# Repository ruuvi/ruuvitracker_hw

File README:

This repository includes RuuviTracker's KiCad project files.

More info about RuuviTracker project: http://www.ruuvitracker.fi

Licensed using: Attribution-NonCommercial-ShareAlike 3.0 Unported (CC BY-NC-SA 3.0)

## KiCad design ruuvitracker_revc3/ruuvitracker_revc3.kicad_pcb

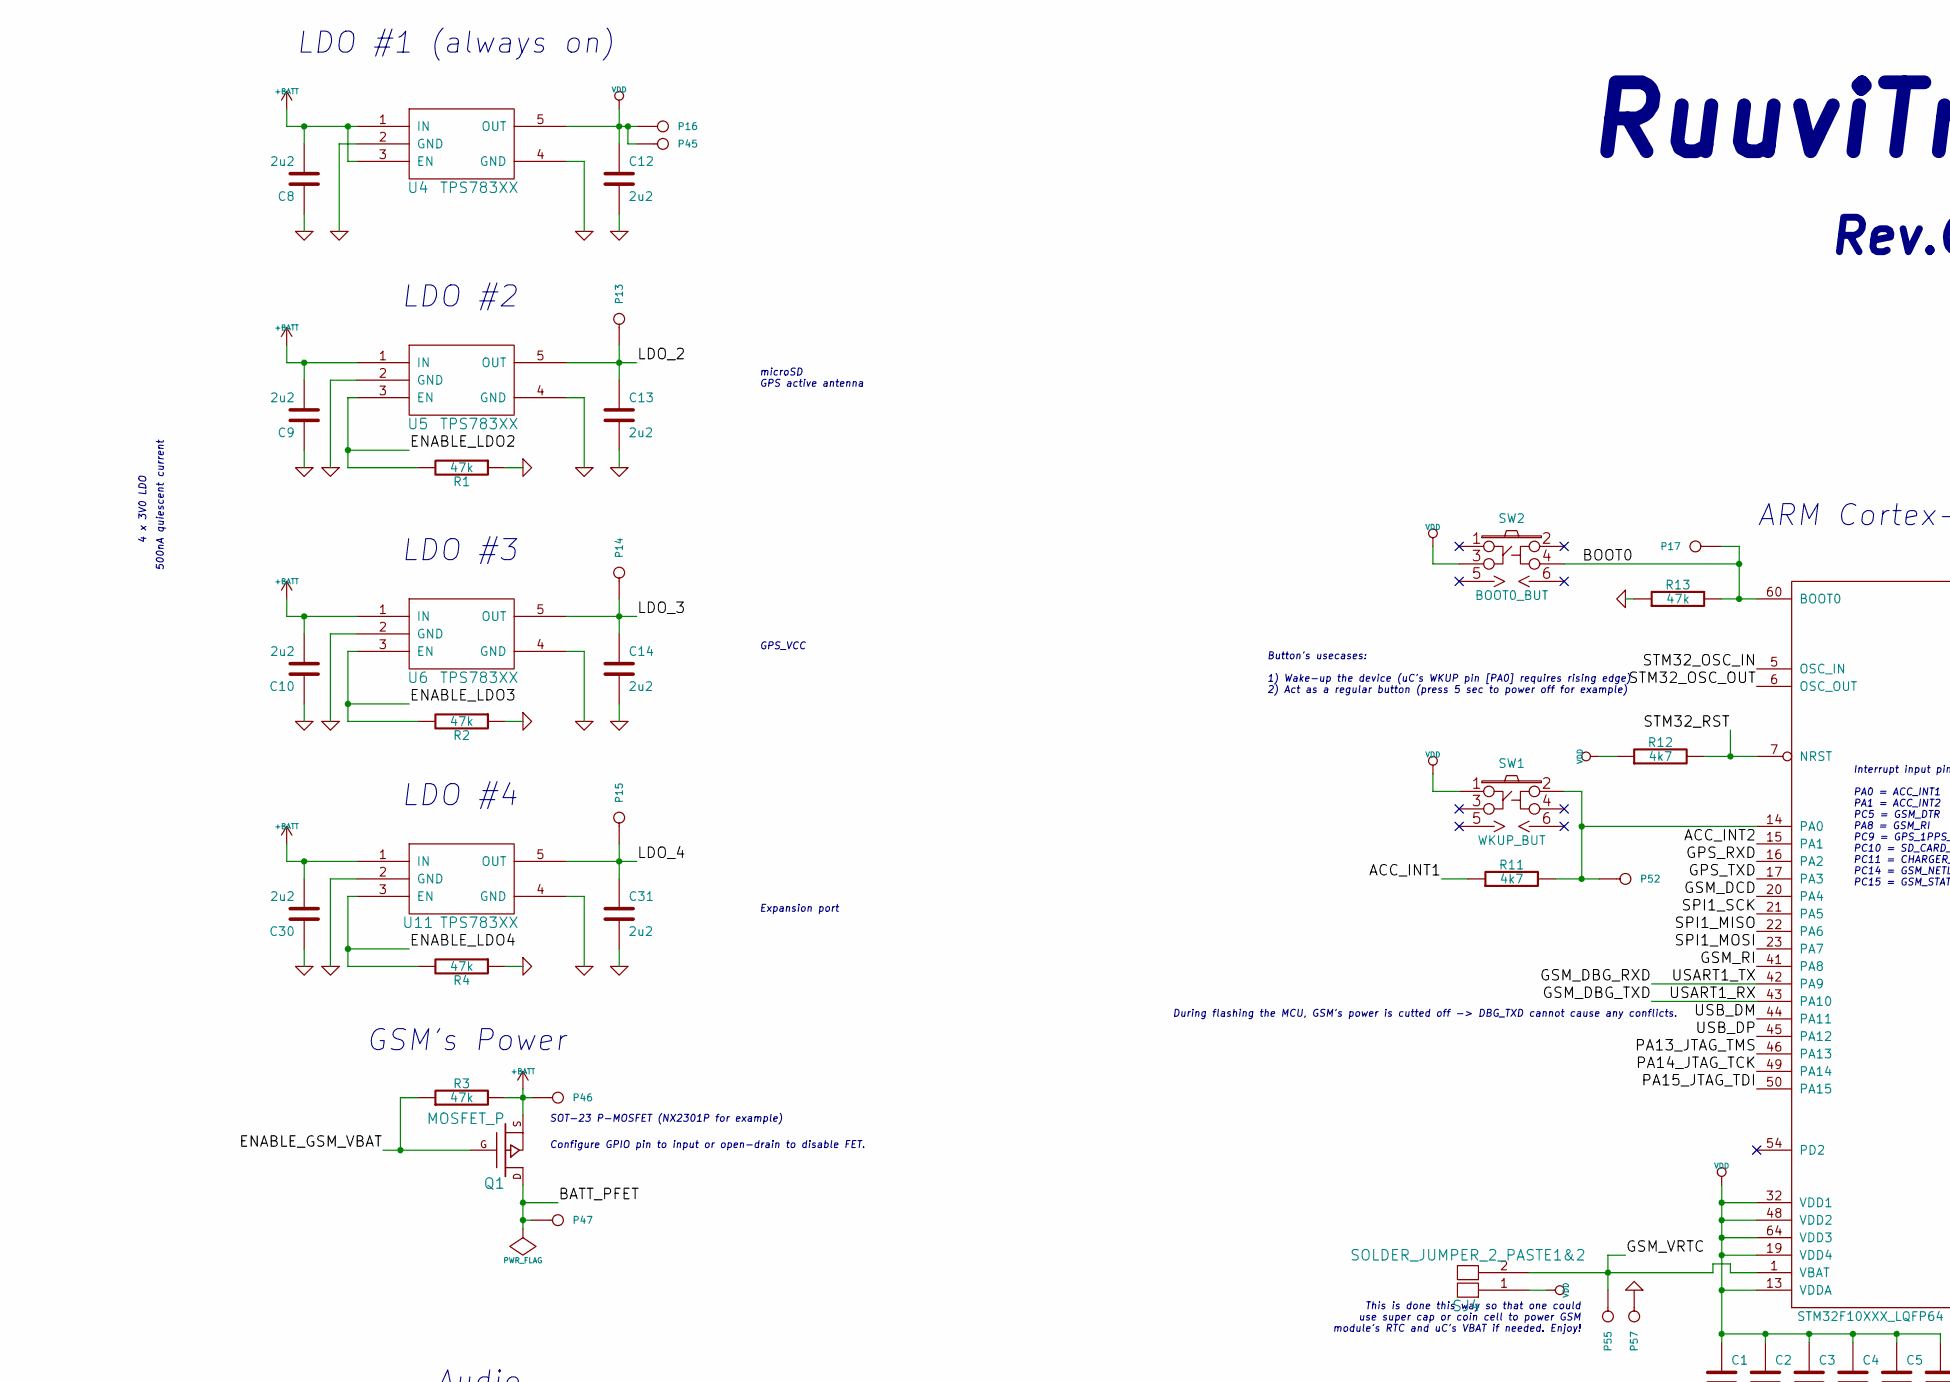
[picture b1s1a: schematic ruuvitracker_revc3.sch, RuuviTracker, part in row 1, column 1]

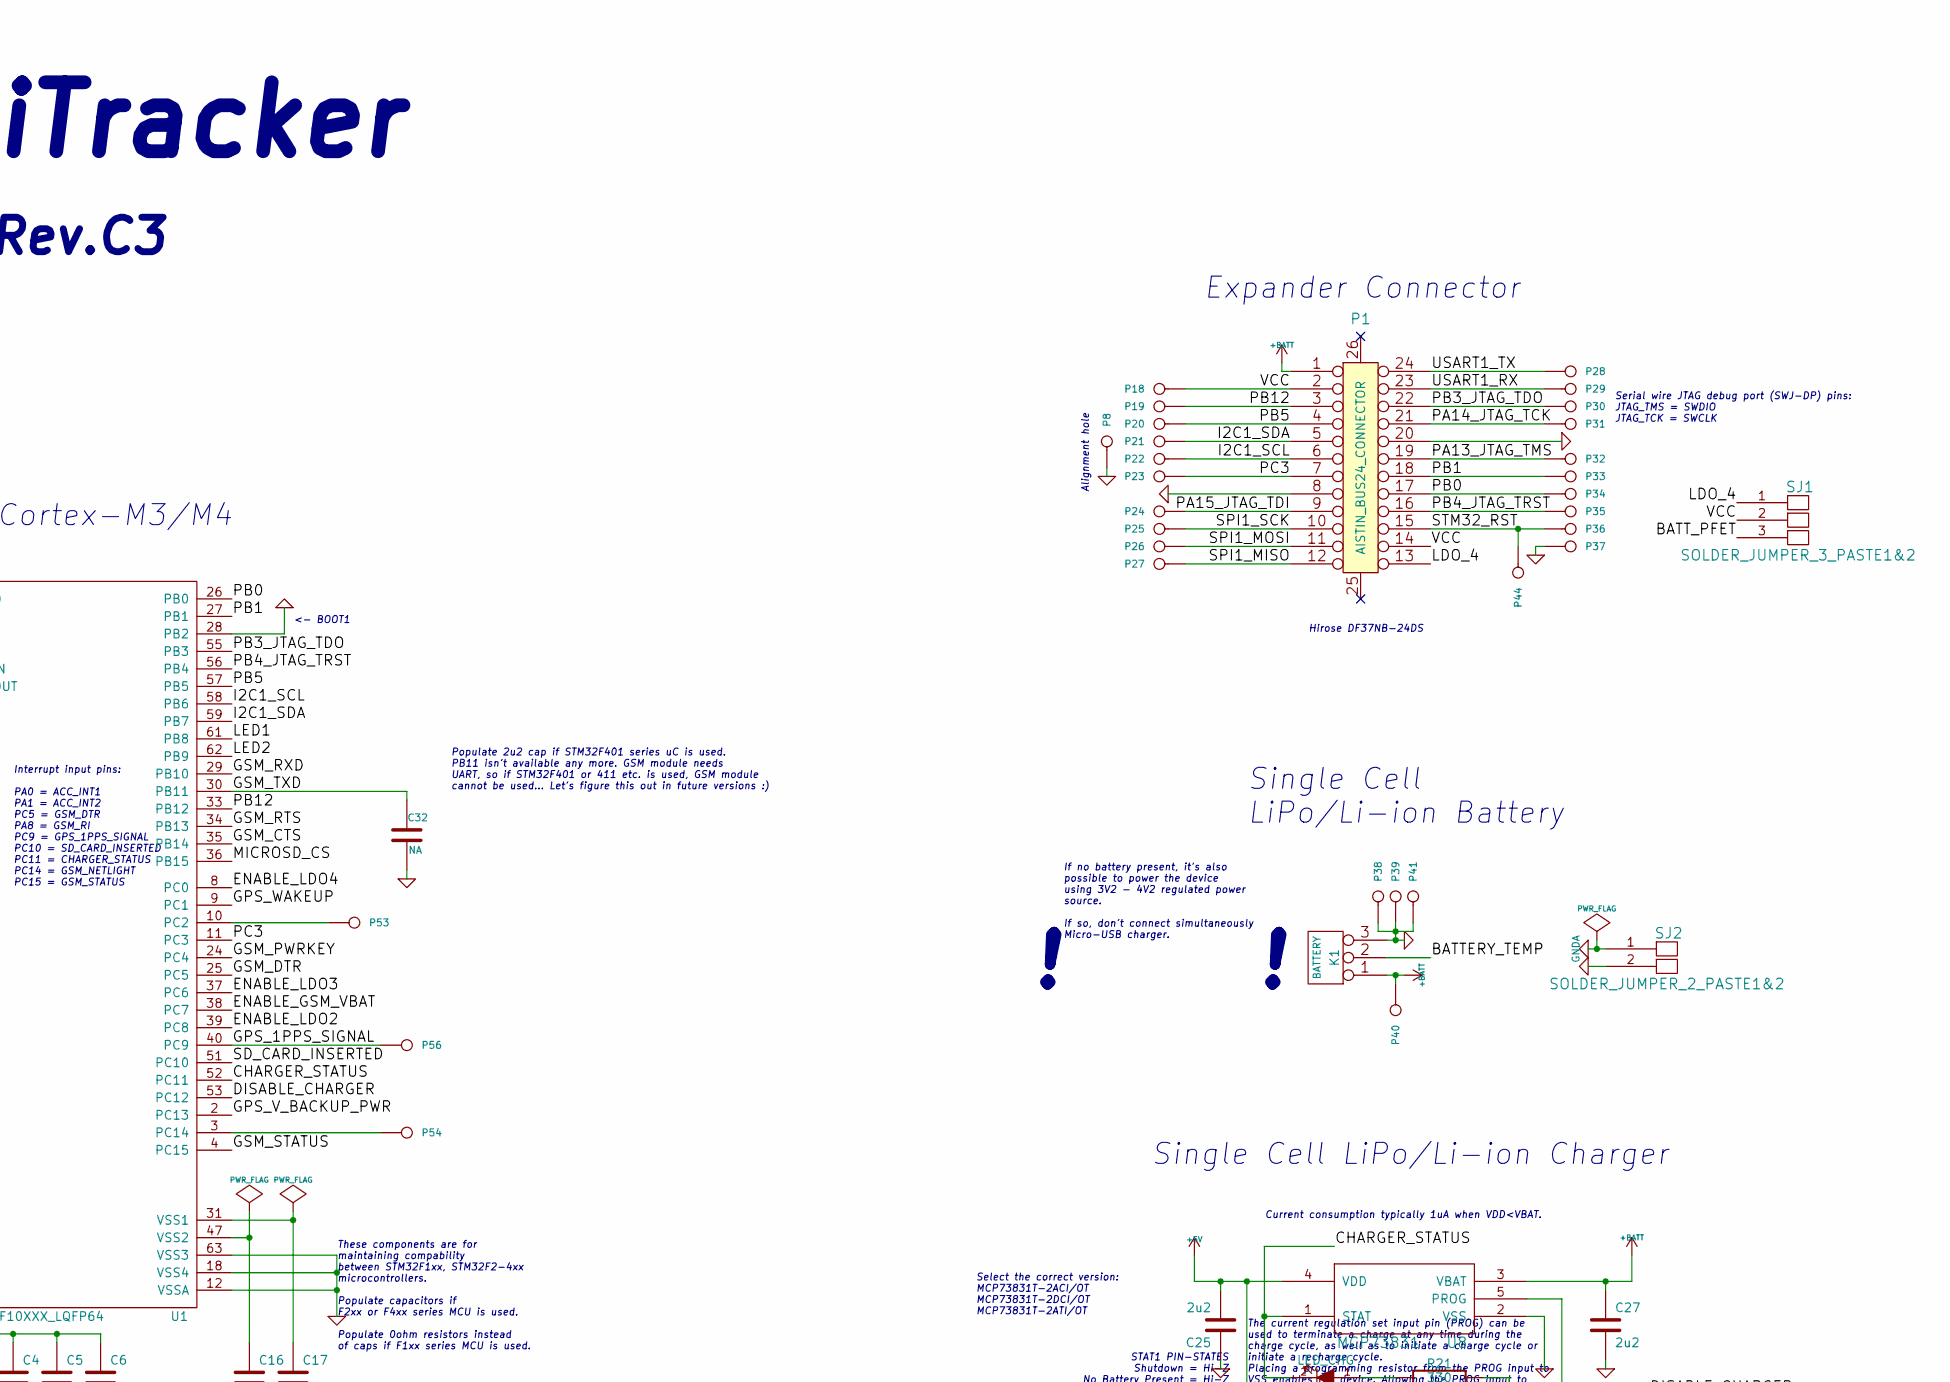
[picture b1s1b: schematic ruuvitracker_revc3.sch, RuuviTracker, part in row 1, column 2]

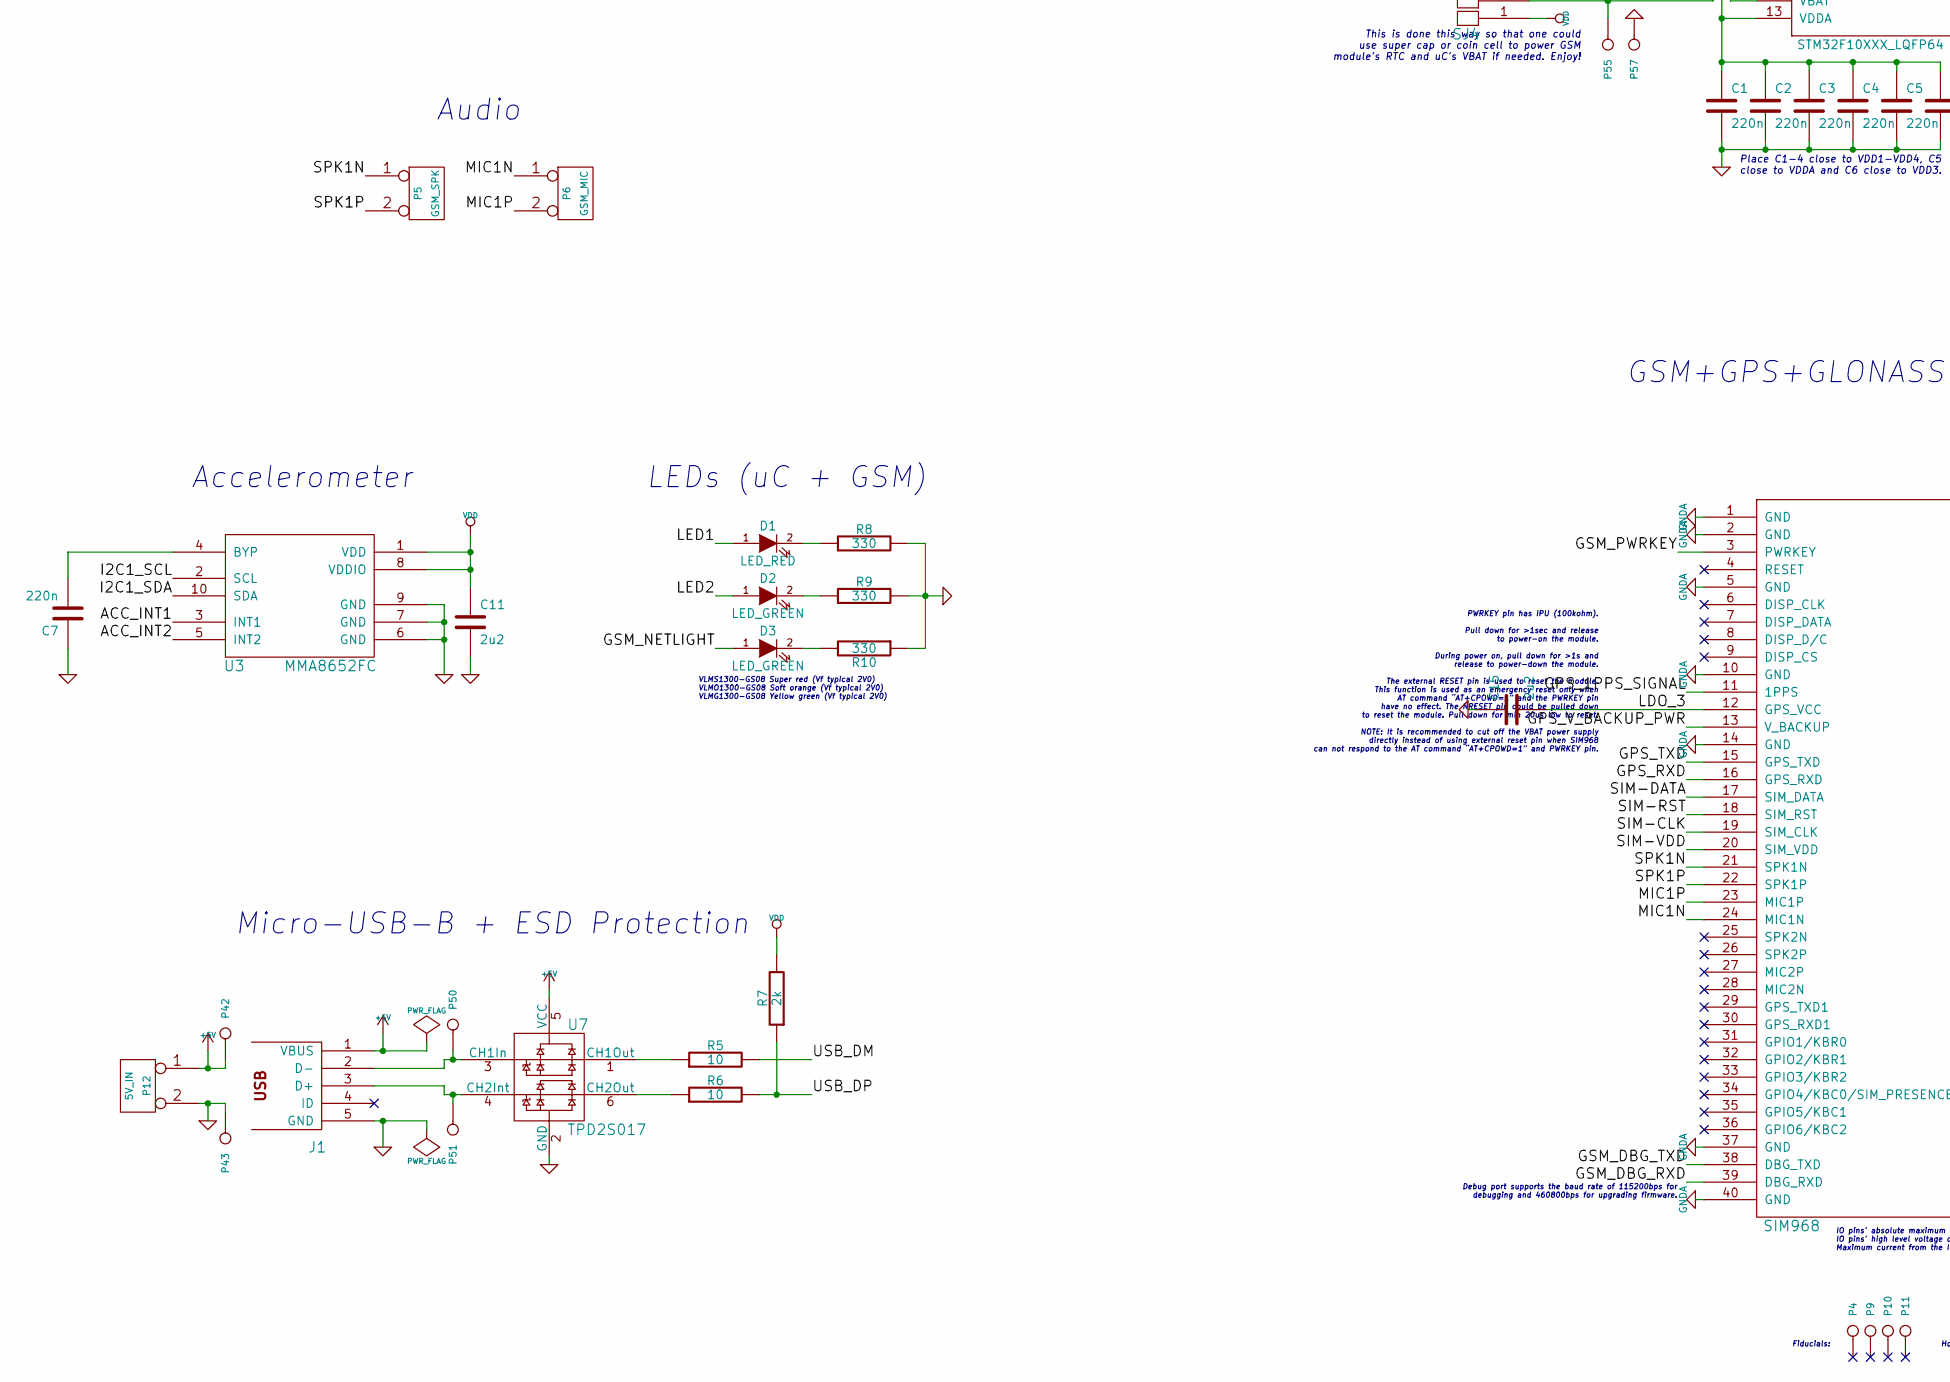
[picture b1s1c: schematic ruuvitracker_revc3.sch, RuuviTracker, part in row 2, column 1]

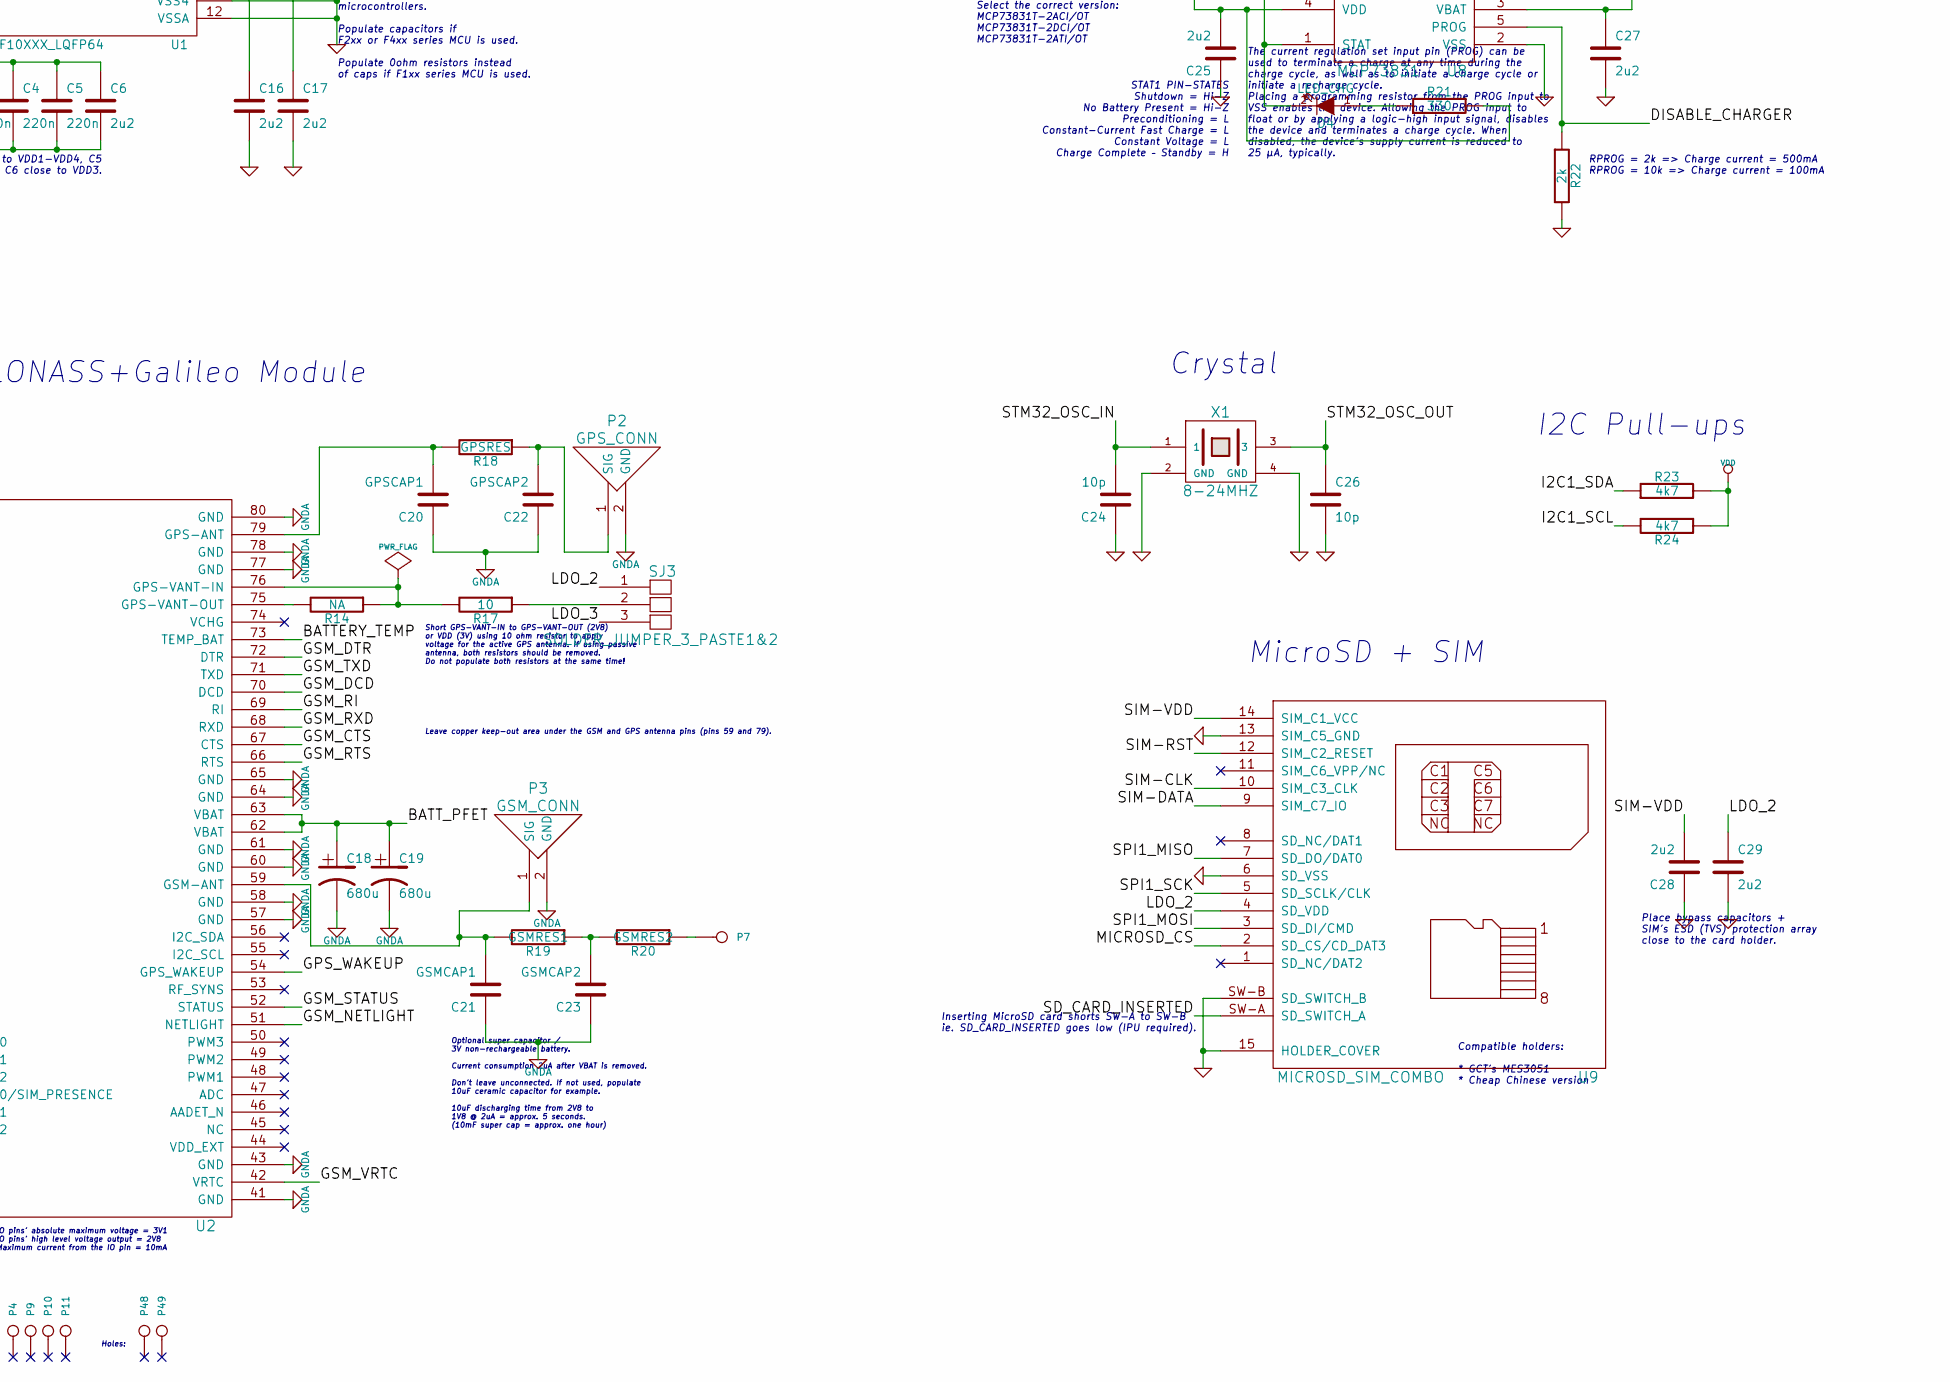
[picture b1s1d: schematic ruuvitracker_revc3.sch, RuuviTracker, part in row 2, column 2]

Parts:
C1, C2, C3, C4, C5, C7: 220n
C6, C8, C9, C10, C11, C12, C13, C14, C15, C16, C17, C25, C27, C28, C29, C30, C31: 2u2
C18, C19: 680u
C20: GPSCAP1
C21: GSMCAP1
C22: GPSCAP2
C23: GSMCAP2
C24, C26: 10p
C32: NA
D1: LED_RED
D2, D3: LED_GREEN
D4: LED_CHG
J1: USB_MICRO_B
K1: BATTERY
P1: AISTIN_BUS24_CONNECTOR
P2: GPS_CONN
P3: GSM_CONN
P4, P9, P10, P11: FIDU
P5: GSM_SPK
P6: GSM_MIC
P7: GSM_ANT
P8: ALIGNMENT
P12: 5V_IN
P13, P14, P15, P16, P17, P18, P19, P20, P21, P22, P23, P24, P25, P26, P27, P28, P29, P30, P31, P32, P33, P34, P35, P36, P37, P38, P39, P40, P41, P42, P43, P44, P45, P46, P47, P50, P51, P52, P53, P54, P55, P56, P57: CONN_1
P48, P49: HOLE
Q1: MOSFET_P
R1, R2, R3, R4, R13: 47k
R5, R6, R17: 10
R7, R22: 2k
R8, R9, R10, R21: 330
R11, R12, R23, R24: 4k7
R14: NA
R18: GPSRES
R19: GSMRES1
R20: GSMRES2
SJ1, SJ3: SOLDER_JUMPER_3_PASTE1&2
SJ2, SJ4: SOLDER_JUMPER_2_PASTE1&2
SW1: WKUP_BUT
SW2: BOOT0_BUT
U1: STM32F10XXX_LQFP64
U2: SIM968
U3: MMA8652FC
U4, U5, U6, U11: TPS783XX
U7: TPD2S017
U8: MCP73831
U9: MICROSD_SIM_COMBO
X1: 8-24MHZ

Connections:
+5V: C25.2, J1.1 (VBUS), P12.1, P42.1, R21.2, U7.5 (VCC), U8.4 (VDD)
+BATT: C8.2, C9.2, C10.2, C27.1, C30.2, K1.1, P1.1, P40.1, P46.1, Q1.S, R3.2, U4.1 (IN), U4.3 (EN), U5.1 (IN), U6.1 (IN), U8.3 (VBAT), U11.1 (IN)
/ACC_INT1: R11.1, U3.3 (INT1)
/ACC_INT2: U1.15 (PA1), U3.5 (INT2)
/BATTERY_TEMP: K1.2 (PM), U2.73 (TEMP_BAT)
/BATT_PFET: C18.1, C19.1, P47.1, Q1.D, SJ1.3, U2.62 (VBAT), U2.63 (VBAT)
/BOOT0: P17.1, R13.2, SW2.4, U1.60 (BOOT0)
/CHARGER_STATUS: D4.2 (K), U1.52 (PC11), U8.1 (STAT)
/DISABLE_CHARGER: R22.1, U1.53 (PC12), U8.5 (PROG)
/ENABLE_GSM_VBAT: Q1.G, R3.1, U1.38 (PC7)
/ENABLE_LDO2: R1.2, U1.39 (PC8), U5.3 (EN)
/ENABLE_LDO3: R2.2, U1.37 (PC6), U6.3 (EN)
/ENABLE_LDO4: R4.2, U1.8 (PC0), U11.3 (EN)
/GPS_1PPS_SIGNAL: P56.1, U1.40 (PC9), U2.11 (1PPS)
/GPS_RXD: U1.16 (PA2), U2.16 (GPS_RXD)
/GPS_TXD: U1.17 (PA3), U2.15 (GPS_TXD)
/GPS_V_BACKUP_PWR: U1.2 (PC13), U2.13 (V_BACKUP)
/GPS_WAKEUP: U1.9 (PC1), U2.54 (GPS_WAKEUP)
/GSM_CTS: U1.35 (PB14), U2.67 (CTS)
/GSM_DBG_RXD: P1.24, P28.1, U1.42 (PA9), U2.39 (DBG_RXD)
/GSM_DBG_TXD: P1.23, P29.1, U1.43 (PA10), U2.38 (DBG_TXD)
/GSM_DCD: U1.20 (PA4), U2.70 (DCD)
/GSM_DTR: U1.25 (PC5), U2.72 (DTR)
/GSM_NETLIGHT: D3.1 (A), U2.51 (NETLIGHT)
/GSM_PWRKEY: U1.24 (PC4), U2.3 (PWRKEY)
/GSM_RI: U1.41 (PA8), U2.69 (RI)
/GSM_RTS: U1.34 (PB13), U2.66 (RTS)
/GSM_RXD: U1.29 (PB10), U2.68 (RXD)
/GSM_STATUS: U1.4 (PC15), U2.52 (STATUS)
/GSM_TXD: C32.1, U1.30 (PB11), U2.71 (TXD)
/GSM_VRTC: P55.1, SJ4.2, U1.1 (VBAT), U2.42 (VRTC)
/I2C1_SCL: P1.6, P22.1, R24.2, U1.58 (PB6), U3.2 (SCL)
/I2C1_SDA: P1.5, P21.1, R23.1, U1.59 (PB7), U3.10 (SDA)
/LDO_2: C13.1, C29.1, P13.1, SJ3.1, U5.5 (OUT), U9.4 (SD_VDD)
/LDO_3: C14.1, C15.2, P14.1, SJ3.3, U2.12 (GPS_VCC), U6.5 (OUT)
/LDO_4: C31.1, P1.13, P15.1, SJ1.1, U11.5 (OUT)
/LED1: D1.1 (A), U1.61 (PB8)
/LED2: D2.1 (A), U1.62 (PB9)
/MIC1N: P6.1, U2.24 (MIC1N)
/MIC1P: P6.2 (PM), U2.23 (MIC1P)
/MICROSD_CS: U1.36 (PB15), U9.2 (SD_CS/CD_DAT3)
/PA13_JTAG_TMS: P1.19, P32.1, U1.46 (PA13)
/PA14_JTAG_TCK: P1.21, P31.1, U1.49 (PA14)
/PA15_JTAG_TDI: P1.9, P24.1, U1.50 (PA15)
/PB0: P1.17, P34.1, U1.26 (PB0)
/PB1: P1.18, P33.1, U1.27 (PB1)
/PB3_JTAG_TDO: P1.22, P30.1, U1.55 (PB3)
/PB4_JTAG_TRST: P1.16, P35.1, U1.56 (PB4)
/PB5: P1.4, P20.1, U1.57 (PB5)
/PB12: P1.3, P19.1, U1.33 (PB12)
/PC3: P1.7, P23.1, U1.11 (PC3)
/SD_CARD_INSERTED: U1.51 (PC10), U9.SW-A (SD_SWITCH_A)
/SIM-CLK: U2.19 (SIM_CLK), U9.10 (SIM_C3_CLK)
/SIM-DATA: U2.17 (SIM_DATA), U9.9 (SIM_C7_IO)
/SIM-RST: U2.18 (SIM_RST), U9.12 (SIM_C2_RESET)
/SIM-VDD: C28.2, U2.20 (SIM_VDD), U9.14 (SIM_C1_VCC)
/SPI1_MISO: P1.12, P27.1, U1.22 (PA6), U9.7 (SD_DO/DAT0)
/SPI1_MOSI: P1.11, P26.1, U1.23 (PA7), U9.3 (SD_DI/CMD)
/SPI1_SCK: P1.10, P25.1, U1.21 (PA5), U9.5 (SD_SCLK/CLK)
/SPK1N: P5.1, U2.21 (SPK1N)
/SPK1P: P5.2 (PM), U2.22 (SPK1P)
/STM32_OSC_IN: C24.2, U1.5 (OSC_IN), X1.1
/STM32_OSC_OUT: C26.1, U1.6 (OSC_OUT), X1.3
/STM32_RST: P1.15, P36.1, P44.1, R12.2, U1.7 (NRST)
/USB_DM: R5.2, U1.44 (PA11)
/USB_DP: R6.2, R7.1, U1.45 (PA12)
/VCC: P1.2, P1.14, P18.1, SJ1.2
GND: C1.2, C2.2, C3.2, C4.2, C5.2, C6.2, C7.1, C8.1, C9.1, C10.1, C11.2, C12.2, C13.2, C14.2, C15.1, C16.2, C17.2, C24.1, C25.1, C26.2, C27.2, C28.1, C29.2, C30.1, C31.2, C32.2, J1.5 (GND), K1.3, P1.8, P1.20, P8.1, P12.2 (PM), P37.1, P38.1, P39.1, P41.1, P43.1, P57.1, R1.1, R2.1, R4.1, R8.2, R9.2, R10.1, R13.1, R22.2, SJ2.2, U1.12 (VSSA), U1.18 (VSS4), U1.28 (PB2), U1.63 (VSS3), U3.6 (GND), U3.7 (GND), U3.9 (GND), U4.2 (GND), U4.4 (GND), U5.2 (GND), U5.4 (GND), U6.2 (GND), U6.4 (GND), U7.2 (GND), U8.2 (VSS), U9.6 (SD_VSS), U9.13 (SIM_C5_GND), U9.15 (HOLDER_COVER), U9.SW-B (SD_SWITCH_B), U11.2 (GND), U11.4 (GND), X1.2 (GND), X1.4 (GND)
GNDA: C18.2, C19.2, C20.1, C21.1, C22.1, C23.1, P2.2 (GND), P3.2 (GND), SJ2.1, U2.1 (GND), U2.2 (GND), U2.5 (GND), U2.10 (GND), U2.14 (GND), U2.37 (GND), U2.40 (GND), U2.41 (GND), U2.43 (GND), U2.57 (GND), U2.58 (GND), U2.60 (GND), U2.61 (GND), U2.64 (GND), U2.65 (GND), U2.77 (GND), U2.78 (GND), U2.80 (GND)
unnamed: P52.1, R11.2, SW1.2, U1.14 (PA0)
unnamed: C16.1, U1.47 (VSS2)
unnamed: C17.1, U1.31 (VSS1)
unnamed: C20.2, R18.2, U2.79 (GPS-ANT)
unnamed: C22.2, P2.1 (SIG), R18.1
unnamed: R17.1, SJ3.2
unnamed: R14.2, U2.75 (GPS-VANT-OUT)
unnamed: R14.1, R17.2, U2.76 (GPS-VANT-IN)
unnamed: P53.1, U1.10 (PC2)
unnamed: P54.1, U1.3 (PC14)
unnamed: J1.3 (D+), P51.1, U7.4 (CH2Int)
unnamed: C21.2, P3.1 (SIG), R19.2, U2.59 (GSM-ANT)
unnamed: C23.2, R19.1, R20.2
unnamed: P7.1, R20.1
unnamed: R6.1, U7.6 (CH2Out)
unnamed: R5.1, U7.1 (CH1Out)
unnamed: J1.2 (D-), P50.1, U7.3 (CH1In)
unnamed: D3.2 (K), R10.2
unnamed: D1.2 (K), R8.1
unnamed: D2.2 (K), R9.1
unnamed: C7.2, U3.4 (BYP)
unnamed: D4.1 (A), R21.1
VDD: C1.1, C2.1, C3.1, C4.1, C5.1, C6.1, C11.1, C12.1, P16.1, P45.1, R7.2, R12.1, R23.2, R24.1, SJ4.1, SW1.1, SW2.3, U1.13 (VDDA), U1.19 (VDD4), U1.32 (VDD1), U1.48 (VDD2), U1.64 (VDD3), U3.1 (VDD), U3.8 (VDDIO), U4.5 (OUT)

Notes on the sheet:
Leave copper keep-out area under the GSM and GPS antenna pins (pins 59 and 79).
IO pins' absolute maximum voltage = 3V1 IO pins' high level voltage output = 2V8 Maximum current from the IO pin = 10mA
Optional super capacitor / 3V non-rechargeable battery. Current consumption 2uA after VBAT is removed. Don't leave unconnected. If not used, populate 10uF ceramic capacitor for example. 10uF discharging time from 2V8 to 1V8 @ 2uA = approx. 5 seconds. (10mF super cap = approx. one hour)
Short GPS-VANT-IN to GPS-VANT-OUT (2V8) or VDD (3V) using 10 ohm resistor to apply voltage for the active GPS antenna. If using passive antenna, both resistors should be removed. Do not populate both resistors at the same time!
PWRKEY pin has IPU (100kohm). Pull down for >1sec and release to power-on the module. During power on, pull down for >1s and release to power-down the module. The external RESET pin is used to reset the module. This function is used as an emergency reset only when AT command “AT+CPOWD=1” and the PW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
GSM+GPS+GLONASS+Galileo Module
These components are for maintaining compability between STM32F1xx, STM32F2-4xx microcontrollers. Populate capacitors if F2xx or F4xx series MCU is used. Populate 0ohm resistors instead of caps if F1xx series MCU is used.
Place C1-4 close to VDD1-VDD4, C5 close to VDDA and C6 close to VDD3.
<- BOOT1
ARM Cortex-M3/M4
Inserting MicroSD card shorts SW-A to SW-B ie. SD_CARD_INSERTED goes low (IPU required).
Compatible holders: * GCT's MES3051 * Cheap Chinese version
! !
If no battery present, it's also possible to power the device using 3V2 - 4V2 regulated power source. If so, don't connect simultaneously Micro-USB charger.
Place bypass capacitors + SIM's ESD (TVS) protection array close to the card holder.
Single Cell LiPo/Li-ion Battery
MicroSD + SIM
I2C Pull-ups
VLMS1300-GS08 Super red (Vf typical 2V0) VLMO1300-GS08 Soft orange (Vf typical 2V0) VLMG1300-GS08 Yellow green (Vf typical 2V0)
LEDs (uC + GSM)
Single Cell LiPo/Li-ion Charger
STAT1 PIN-STATES Shutdown = Hi-Z No Battery Present = Hi-Z Preconditioning = L Constant-Current Fast Charge = L Constant Voltage = L Charge Complete – Standby = H
The current regulation set input pin (PROG) can be used to terminate a charge at any time during the charge cycle, as well as to initiate a charge cycle or initiate a recharge cycle. Placing a programming resistor from the PROG input to VSS enables the device. Allowing the PROG input to float or by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
RPROG = 2k => Charge current = 500mA RPROG = 10k => Charge current = 100mA
Accelerometer
Crystal
Debug port supports the baud rate of 115200bps for debugging and 460800bps for upgrading firmware.
Serial wire JTAG debug port (SWJ-DP) pins: JTAG_TMS = SWDIO JTAG_TCK = SWCLK
500nA quiescent current
LDO #1 (always on)
Audio
Micro-USB-B + ESD Protection
GSM's Power
SOT-23 P-MOSFET (NX2301P for example)
LDO #2
Configure GPIO pin to input or open-drain to disable FET.
Button's usecases: 1) Wake-up the device (uC's WKUP pin [PA0] requires rising edge) 2) Act as a regular button (press 5 sec to power off for example)
RuuviTracker
Rev.C3
Current consumption typically 1uA when VDD<VBAT.

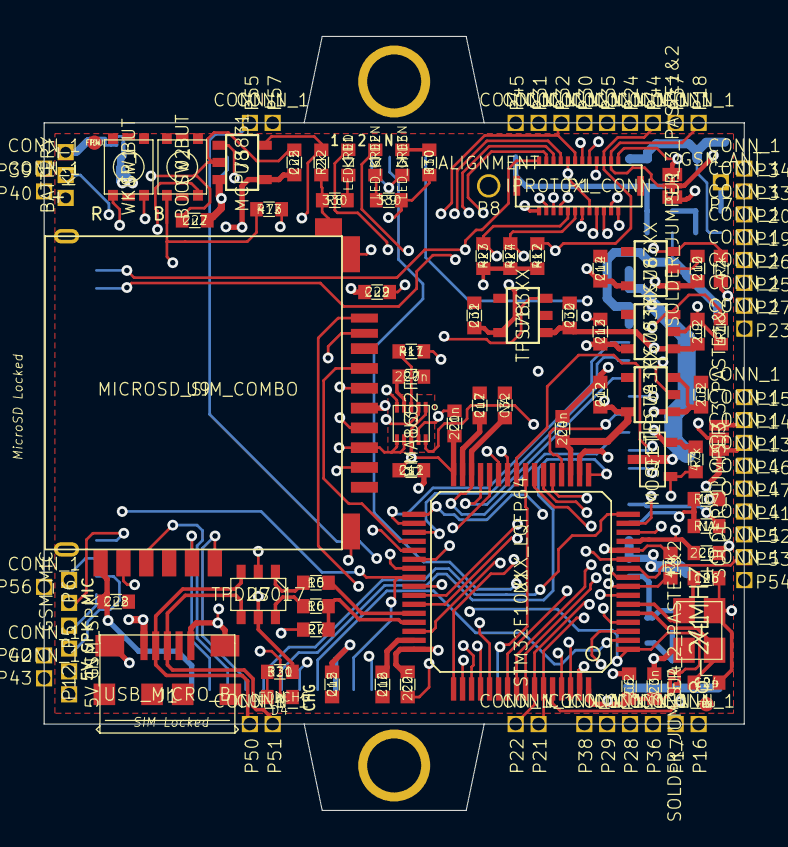
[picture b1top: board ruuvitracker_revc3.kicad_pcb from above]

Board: 6 copper layers, 38.9 x 43.0 mm, 135 parts (0 on the bottom side), 92 nets.

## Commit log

2012-01-07 Initial commit.
2012-01-07 New file: ruuvitracker-cache.lib
2012-01-07 Modified README
2012-01-12 Added some logic to detect Micro-USB charger properly + some minor bug fixes.
2012-01-14 Some fixes to schematic, created new footprints and .brd file.
    Fixed:
    - Mirrored MicroSD schematic component
    Created:
    - Over 10 new footprints
    - .cmp file
    - .brd file
2012-01-14 Modified few footprints, continued component placement.
2012-01-14 Component placement almost ready. PCB shrinked from 55x37mm to 50x30mm.
2012-01-14 Component placement almost ready. PCB shrinked from 55x37mm to 50x37mm.
2012-01-15 Added two 3mm holes. No routing done yet. Component placement almost ok.
2012-01-15 Almost all traces routed. Still 2-layer board, jei! :-)
2012-01-16 All traces routed and DRC passed!
2012-01-17 PCB 99% ready. Add .gitignore.
2012-01-17 Freezing to REVA.
2012-01-17 Modified component references on PCB (better alignment).
2012-01-18 Added dimensions of the board.
2012-01-19 Added kicad_lib folder with few 3D models.
2012-01-19 Added info about license.
2012-01-19 Fixed 3D models' paths.
2012-01-19 Added ../kicad_lib/packages3d to user defined search paths.
2012-01-19 Fixed 3D model paths...
2012-01-19 Fixed eeschema library problems.
2012-01-22 New 3D models for card slot and MicroUSB connector.
2012-01-23 Added 3D model for crystal and fixed card slot's 3D model.
2012-09-23 RevB initial commit.
2012-09-27 New MCU and totally new schema layout.
2012-10-20 Add new charger IC
2012-10-20 Modify project's domain
2012-11-15 Add MEMS microphone and some minor mods.
2012-11-25 New LDO.
2012-11-25 Remove STM32F1xx support.
2012-11-25 New LED layout and some other minor mods.
2012-11-25 Add EEPROM IC.
2012-12-08 Minor mods.
2012-12-08 New pwr switch and expander connector
2012-12-08 Remove speaker's and mic's caps to save space
2012-12-08 Add external audio amp
2012-12-09 Minor mods
2012-12-18 New USB OTG EMI protection IC
2012-12-20 USB ESD modifications
2012-12-20 Another ESD IC replacement
2012-12-22 Add testpoints
2012-12-22 New level-shifter IC
2012-12-22 New buttons
2012-12-23 Some thinking about pinouts
2012-12-23 Some pin arrangement
2012-12-23 Little more pin arrangement
2012-12-23 New expander layout
2012-12-23 Charging circuitry finished
2012-12-23 First "final" version
2012-12-24 First final annotated RevB schematics version
2012-12-24 Add alternative voltage source for GPS active antennas
2012-12-24 Some corrections for texts
2012-12-24 Change IO Expander's pinout
2012-12-26 New footprints
2012-12-26 New schema component
2012-12-26 Add gyroscope
2012-12-26 Pinout arrangement
2012-12-26 New EEPROM
2012-12-26 Replace EEPROM IC
2012-12-26 New gyro
2012-12-26 Replace gyroscope IC
2012-12-26 New schema draft
2012-12-26 Update LGA14 according Freescale's AN3484 appnote
2012-12-27 Made according STM's specs
2012-12-27 Modified module's footprint
2012-12-27 Made according TI's specs
2012-12-27 Remove GSM_STATUS LED
2012-12-28 Add 1Mohm pull-down resistors to ensure known pinstates during bootloader's detection phase.
2012-12-28 Add batt voltage divider and P-MOSFETs for GSM and SD
2012-12-29 Small fixes (pwr switch, fet gates' io pins etc.)
2012-12-29 Another schema draft
2012-12-29 Add P-MOSTET to enable SYSTEM_LOAD only using pwr switch
2012-12-29 Update schema draft
2012-12-29 Small mods
2012-12-29 New connector for expander1
2012-12-29 Replace 26pin expander#1 with 26x2 expander
2012-12-30 Made according TI's specs (paste layer's clearance 0,01mm smaller [+0,01mm instead of +0,02mm] than TI suggests)
2012-12-30 Minor mods, PA9-PA12 available on expansion connector
2012-12-30 Made almost according specs, should work perfectly
2012-12-30 Fix pads positions
2012-12-30 Made according specs, but slightly narrowed pads (0,35mm vs. 0,40mm) and little closer together than ref design recommends
2012-12-30 Made according Alps' specs
2012-12-30 Made according Panasonic EXB2HV resistor array's specs
2012-12-30 Made according Panasonic EXB28V resistor array's specs
2012-12-30 Replace 8xres arrays with 4xres arrays
2012-12-30 Few mods made after draft#003
2012-12-30 Add charger diodes, ferrite to MEMS MIC's power etc.
2012-12-31 Add common zener diode schema symbol
2012-12-31 Some fixes
2012-12-31 Add zener and remove schottkys
2012-12-31 Remove GSM's MIC, fix GSM's audio amp circuitry, own voltage divider for high_voltage input
2013-01-01 New draft
2013-01-01 New TI's load switch component schema symbol
2013-01-01 Replace P-MOSFETs with load switches etc.
2013-01-03 Hopefully final schema with P-MOSFETs
2013-01-03 Common TVS diode schema symbol
2013-01-03 Revert back to P-MOSFET topology (USB voltage protection). Common-drain-pmos. Used often with the OTG.
2013-01-04 Made according IR's specs
2013-01-04 Minor fixes
2013-01-04 Remove OTG_CURRENT_LIMIT_SELECTION pin's pull-down resistor. Connect charger's status led's power to PMOS's source side.
2013-01-05 Made almost according Gradconn's specs. Only slightly smaller thru-holes.
2013-01-05 Modify module attributs: "Normal + insert"
2013-01-05 New general 0,05 inch pitch thru-hole connector
2013-01-05 Made almost according available general MSOP-8 specs
2013-01-06 Molex 1,25mm pitch connectors should fit both ways (reverse pin order)
2013-01-06 Laird's footprint was a mess, shrinked pans from 1mm to 0,4mm.
2013-01-06 File name says it all
2013-01-06 Made slightly according ON Semi's specs (inaccurate ones)
2013-01-06 Made almost according AVX's specs (pads slightly closer together)
2013-01-06 Made according AVX's specs
2013-01-06 Some text mods
2013-01-06 Made according Panasonics's and mine specs
2013-01-06 Pads closer together (just a little)
2013-01-06 Made according Abracon's specs
2013-01-06 Made according Vishay's specs
2013-01-06 Some text addons
2013-01-07 'Final' schematics
2013-01-07 General 0,5mm fidu/testpoint smd pad (no paste layer)
2013-01-07 Folder for exported material
2013-01-07 Fix pinout
2013-01-07 Initial commit for RuuviTracker RevB's PCB layout design process
2013-01-07 First components on the board
2013-01-08 Fix text's position
2013-01-08 More components on the board
2013-01-08 PCB outlines done
2013-01-08 Can be used for BMIS-201-C
2013-01-08 Change EMI shield's footprint and finish pcb outlines
2013-01-08 Place more components
2013-01-09 Fix thru holes
2013-01-09 Add silkscreen
2013-01-09 Some layout progress
2013-01-09 Some progress, more components on the board etc.
2013-01-09 Some progress
2013-01-09 Almost all components placed
2013-01-10 All components on the board, finetuning begins...
2013-01-11 Fix footprint's NPTH
2013-01-11 More progress and few new test points
2013-01-12 Some minor schema fixes and more pcb layour progress
2013-01-12 IO expander pin changes etc.
2013-01-12 SMD test point
2013-01-12 Add DCDC's zones etc.
2013-01-13 Power planes done
2013-01-13 More progress
2013-01-13 Better uC's bypass cap positioning, gyro from top to bottom
2013-01-13 90ohm matched usb bus
2013-01-13 Progress
2013-01-13 I2C bus done
2013-01-13 ID + MCU VBUS done
2013-01-13 Better DCDC layout
2013-01-13 Part of IO lines ready
2013-01-13 More IO lines ready
2013-01-14 All IO lines ready
2013-01-15 RT footprints
2013-01-15 Almost done
2013-01-16 Logos ok, few traces left, DRC almost passed
2013-01-16 Most recent schema
2013-01-16 DRC almost passed, few disconnected pins
2013-01-16 DRC passed (one pin unconnected, but it's KiCad's bug)
2013-01-16 Move haptic driver's bypass caps
2013-01-16 Add GND zones to in1&2 layers
2013-01-17 New awesome footprints :)
2013-01-17 Make PCB look really awesome
2013-01-17 Add Netlight text. PCB order is on!
2013-01-18 100nF caps to 1uF
2013-01-18 Improvised SO8N footprint
2013-01-18 Change EEPROMs footprint from TSSOP8 to SO8N
2013-01-30 Add comment about GSM_PWRKEY's states
2013-01-30 RevB draft#007 -> Rev.B1
2013-01-30 First PCBs ordered according this one
2013-11-21 started making the part for the connector header but flaked out
2013-11-26 generated with ULP
2013-11-26 regenerated
2013-11-26 add the tabs
2013-11-26 make the device
2013-11-26 ignore eagle backup files too
2013-12-01 started working on a simple breakout
2013-12-01 add SWD connector, though the VCC might *not* be (even equivalent to) the STM32 VDD, which would be a major problem
2013-12-01 The VCCs might not be the same, at least not in the future...
2013-12-01 use solder jumpers to select which "vcc" pin to use for SWD VDD
2013-12-01 add reset switch
2013-12-01 receptable on top of board, header at bottom
2013-12-01 updated the df37 library changes
2013-12-01 hirose datasheet for future reference
2014-01-30 wrote this down before soldering it
2014-01-30 added a note about how to patch the board for this
2014-03-16 notes on c2
2014-03-16 for those who hate eagle
2014-05-19 pinout for revC2, with source material
2015-03-15 ignore osx temp/md files
2015-03-15 remove old revb stuff
2015-03-15 remove the C2 stuff
2015-03-15 reorg
2015-03-15 the master is only a pointer to the other branches
2015-03-15 forgot to delete this
2015-03-15 fix the link
2015-07-11 Initial library commit
2015-07-11 Rev.C related docs
2015-07-11 RuuviTracker in Chiang Mai, Thailand

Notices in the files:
ruuvitracker_revc3/ruuvitracker_revc3.sch:
http://creativecommons.org/licenses/by-sa/4.0
License: Attribution-ShareAlike 4.0 International (CC BY-SA 4.0)
